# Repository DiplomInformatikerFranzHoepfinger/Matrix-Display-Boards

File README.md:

# Matrix-Display-Boards

## Inspiration

### Lytec

[CL3000 Photos](CL3000.md)

http://www.lytec.cn/CL3000?_l=en

http://www.lytec.cn/CL3000-N?product_id=37&_l=en

### Adafruit

https://github.com/adafruit/Adafruit-MatrixPortal-S3-PCB

### SmartMatrix / pixelmatix

https://community.pixelmatix.com/t/want-to-drive-a-hub08-display/1491

https://github.com/pixelmatix/SmartMatrix

https://github.com/pixelmatix/SmartMatrix/tree/master/extras/hardware

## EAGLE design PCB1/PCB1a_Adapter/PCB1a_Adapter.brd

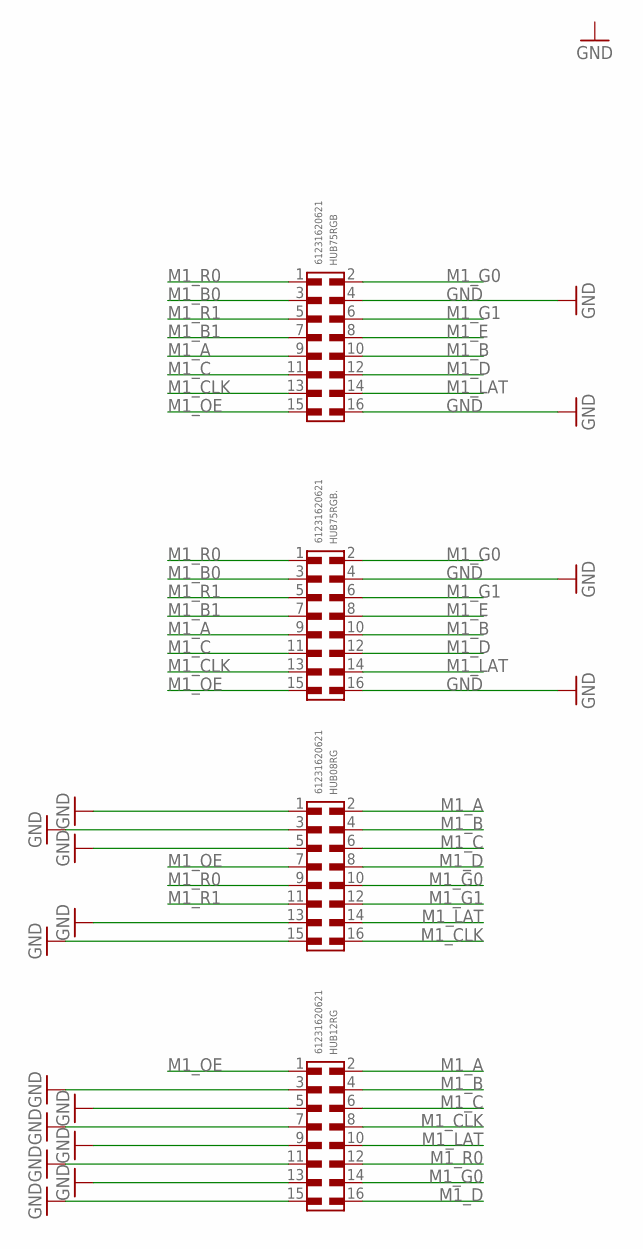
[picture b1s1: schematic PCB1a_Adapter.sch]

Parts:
HUB08RG, HUB12RG, HUB75RGB, HUB75RGB.: 61231620621

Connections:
GND: HUB08RG.1, HUB08RG.3, HUB08RG.5, HUB08RG.13, HUB08RG.15, HUB12RG.3, HUB12RG.5, HUB12RG.7, HUB12RG.9, HUB12RG.11, HUB12RG.13, HUB12RG.15, HUB75RGB.4, HUB75RGB.16, HUB75RGB..4, HUB75RGB..16
M1_A: HUB08RG.2, HUB12RG.2, HUB75RGB.9, HUB75RGB..9
M1_B: HUB08RG.4, HUB12RG.4, HUB75RGB.10, HUB75RGB..10
M1_B0: HUB75RGB.3, HUB75RGB..3
M1_B1: HUB75RGB.7, HUB75RGB..7
M1_C: HUB08RG.6, HUB12RG.6, HUB75RGB.11, HUB75RGB..11
M1_CLK: HUB08RG.16, HUB12RG.8, HUB75RGB.13, HUB75RGB..13
M1_D: HUB08RG.8, HUB12RG.16, HUB75RGB.12, HUB75RGB..12
M1_E: HUB75RGB.8, HUB75RGB..8
M1_G0: HUB08RG.10, HUB12RG.14, HUB75RGB.2, HUB75RGB..2
M1_G1: HUB08RG.12, HUB75RGB.6, HUB75RGB..6
M1_LAT: HUB08RG.14, HUB12RG.10, HUB75RGB.14, HUB75RGB..14
M1_OE: HUB08RG.7, HUB12RG.1, HUB75RGB.15, HUB75RGB..15
M1_R0: HUB08RG.9, HUB12RG.12, HUB75RGB.1, HUB75RGB..1
M1_R1: HUB08RG.11, HUB75RGB.5, HUB75RGB..5

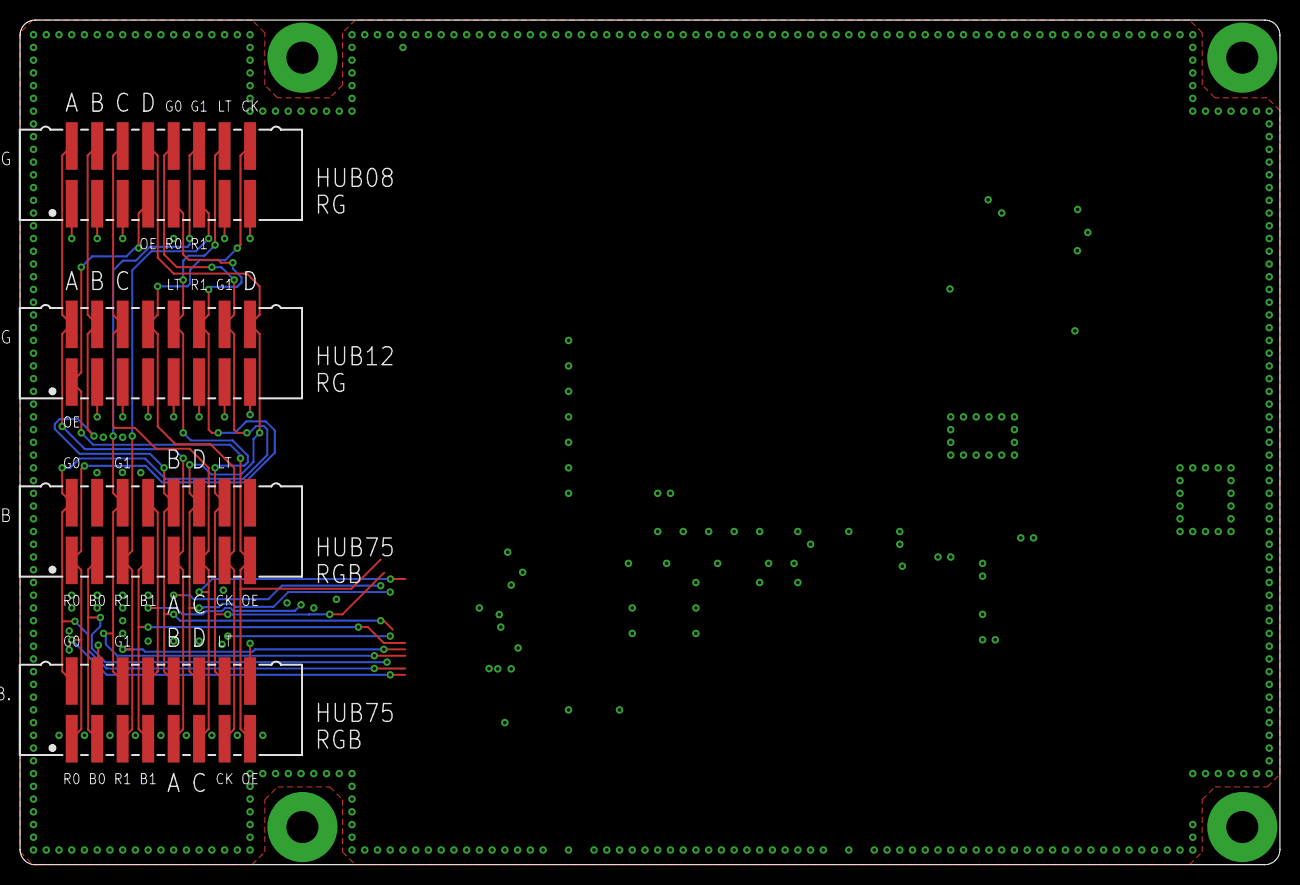
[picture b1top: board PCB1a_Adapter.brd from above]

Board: 2 copper layers, 125.6 x 84.2 mm, 4 parts (0 on the bottom side), 15 nets.

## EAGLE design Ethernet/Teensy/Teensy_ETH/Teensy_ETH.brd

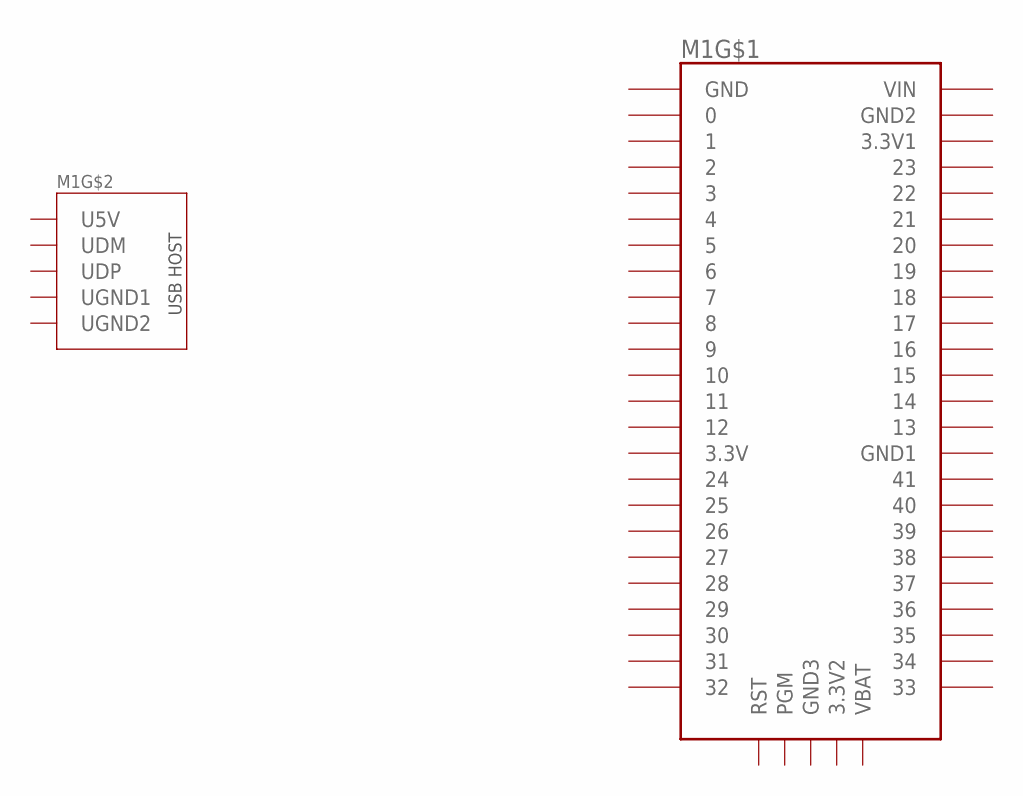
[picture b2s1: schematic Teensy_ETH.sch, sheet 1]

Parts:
M1: TEENSY4.1

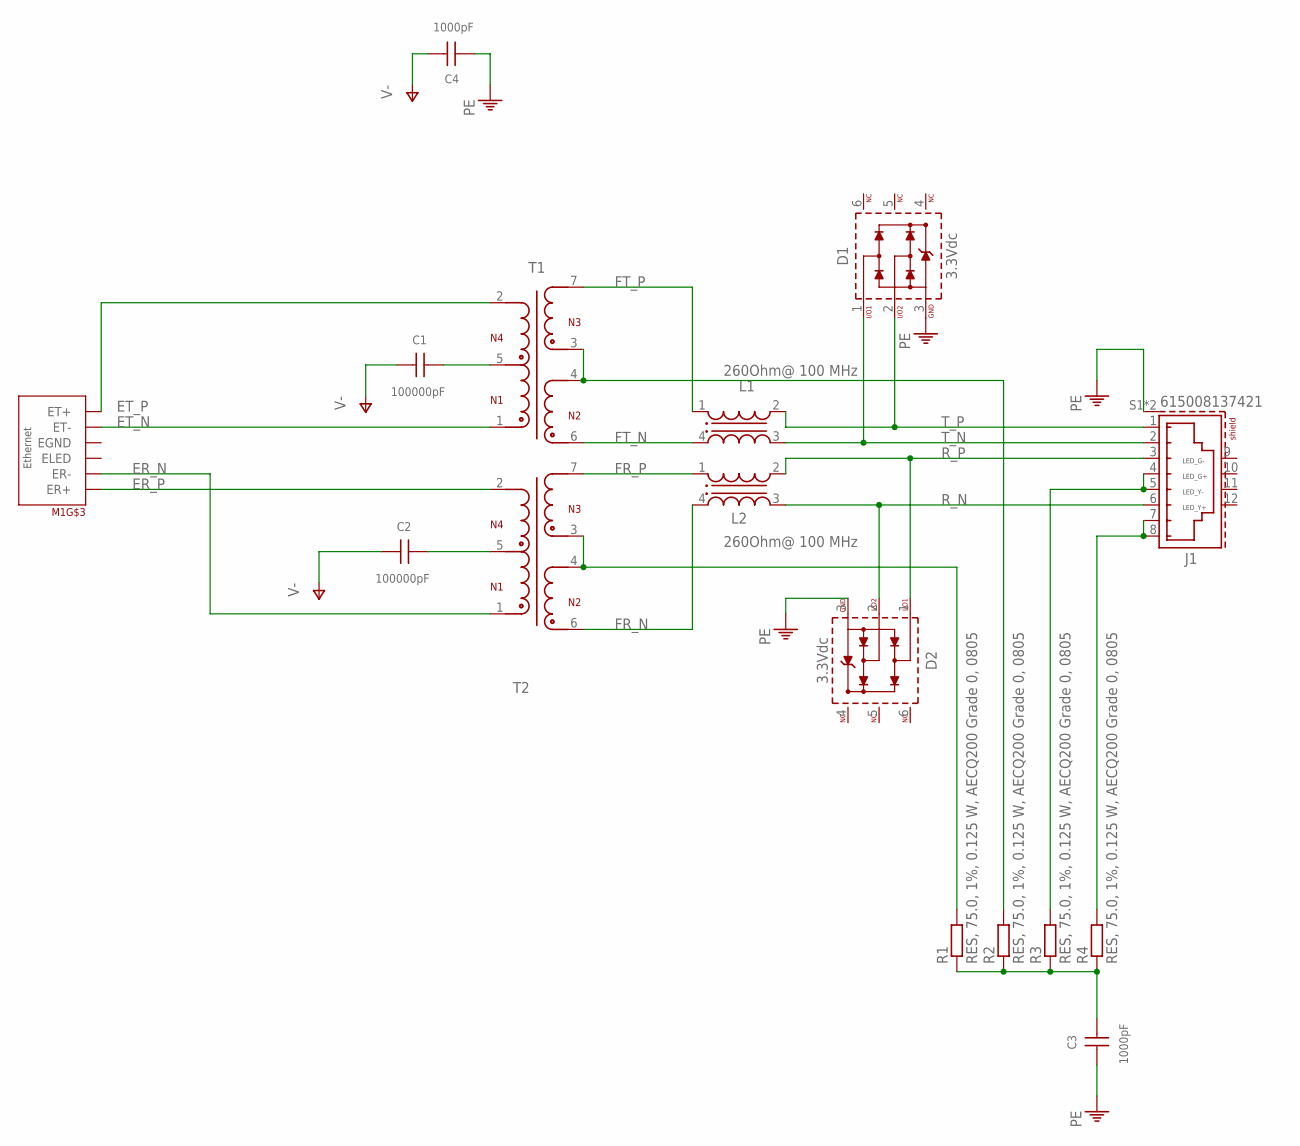
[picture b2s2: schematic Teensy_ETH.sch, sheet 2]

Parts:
C1, C2: 100000pF; WCAP-CSST_0603_R
C3, C4: 1000pF; WCAP-CSMH_1206_H1.6_R
D1, D2: 3.3Vdc; WE-TVS_DFN1210-6L
J1: 615008137421
L1, L2: 260Ohm@ 100 MHz; WE-CNSW_0805
M1: TEENSY4.1
R1, R2, R3, R4: RES, 75.0, 1%, 0.125 W, AECQ200 Grade 0, 0805; R0805
T1, T2: WE-STST_4532_74930000; WE-STST_74930000

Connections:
ER_N: M1.ER-, T2.1
ER_P: M1.ER+, T2.2
ET_N: M1.ET+ (ET-), T1.1
ET_P: M1.ET- (ET+), T1.2
FR_N: L2.4 (1), T2.6
FR_P: L2.1 (4), T2.7
FT_N: L1.4 (1), T1.6
FT_P: L1.1 (4), T1.7
unnamed: R2.2, T1.3, T1.4
unnamed: R1.2, T2.3, T2.4
unnamed: J1.4, J1.5, R3.2
unnamed: J1.7, J1.8, R4.2
unnamed: C1.2, T1.5
unnamed: C2.2, T2.5
unnamed: C3.2, R1.1, R2.1, R3.1, R4.1
PE: C3.1, C4.1, D1.3 (GND), D2.3 (GND), J1.S1 (SHIELD), J1.S2 (SHIELD)
R_N: D2.2 (I/O2), J1.6, L2.3 (2)
R_P: D2.1 (I/O1), J1.3, L2.2 (3)
T_N: D1.1 (I/O1), J1.2, L1.3 (2)
T_P: D1.2 (I/O2), J1.1, L1.2 (3)
V-: C1.1, C2.1, C4.2

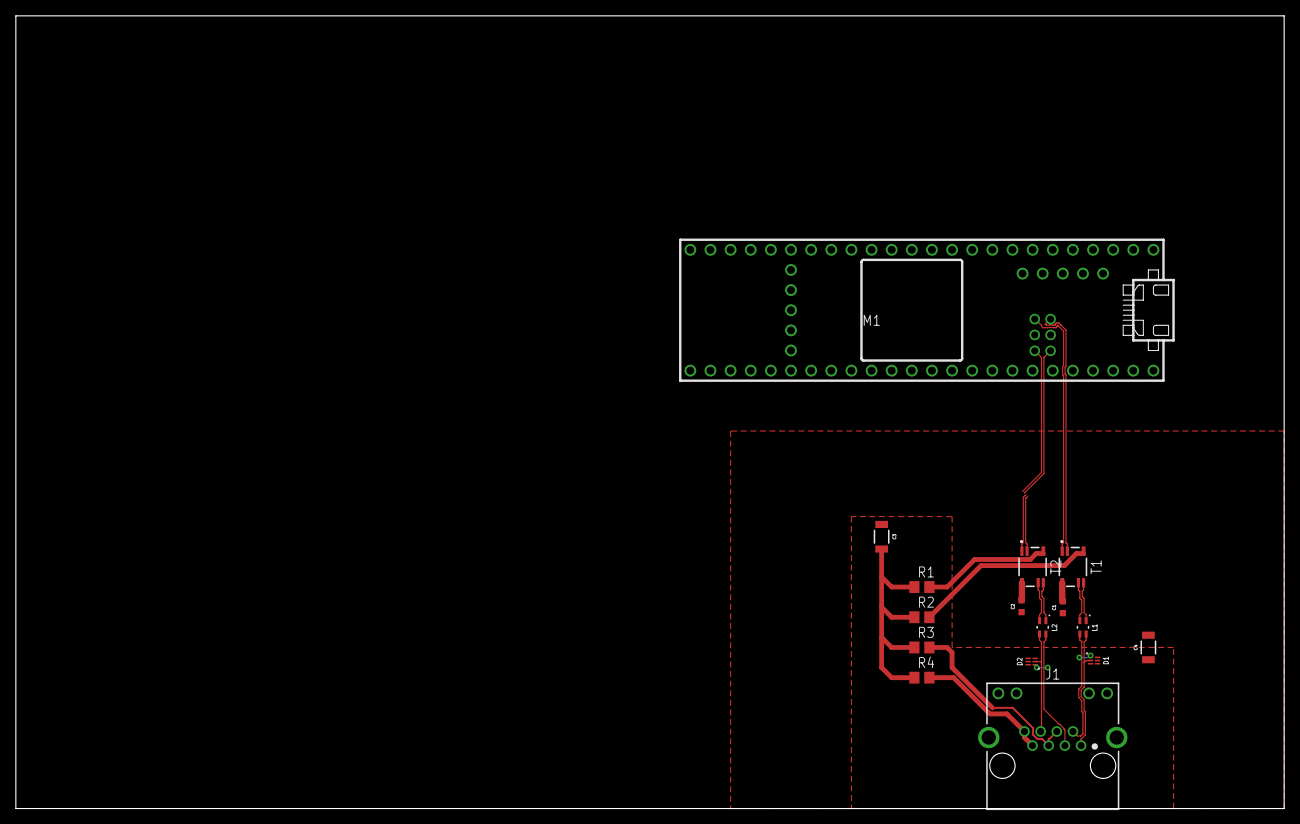
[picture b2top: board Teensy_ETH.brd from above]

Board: 2 copper layers, 160.0 x 100.0 mm, 16 parts (0 on the bottom side), 21 nets.

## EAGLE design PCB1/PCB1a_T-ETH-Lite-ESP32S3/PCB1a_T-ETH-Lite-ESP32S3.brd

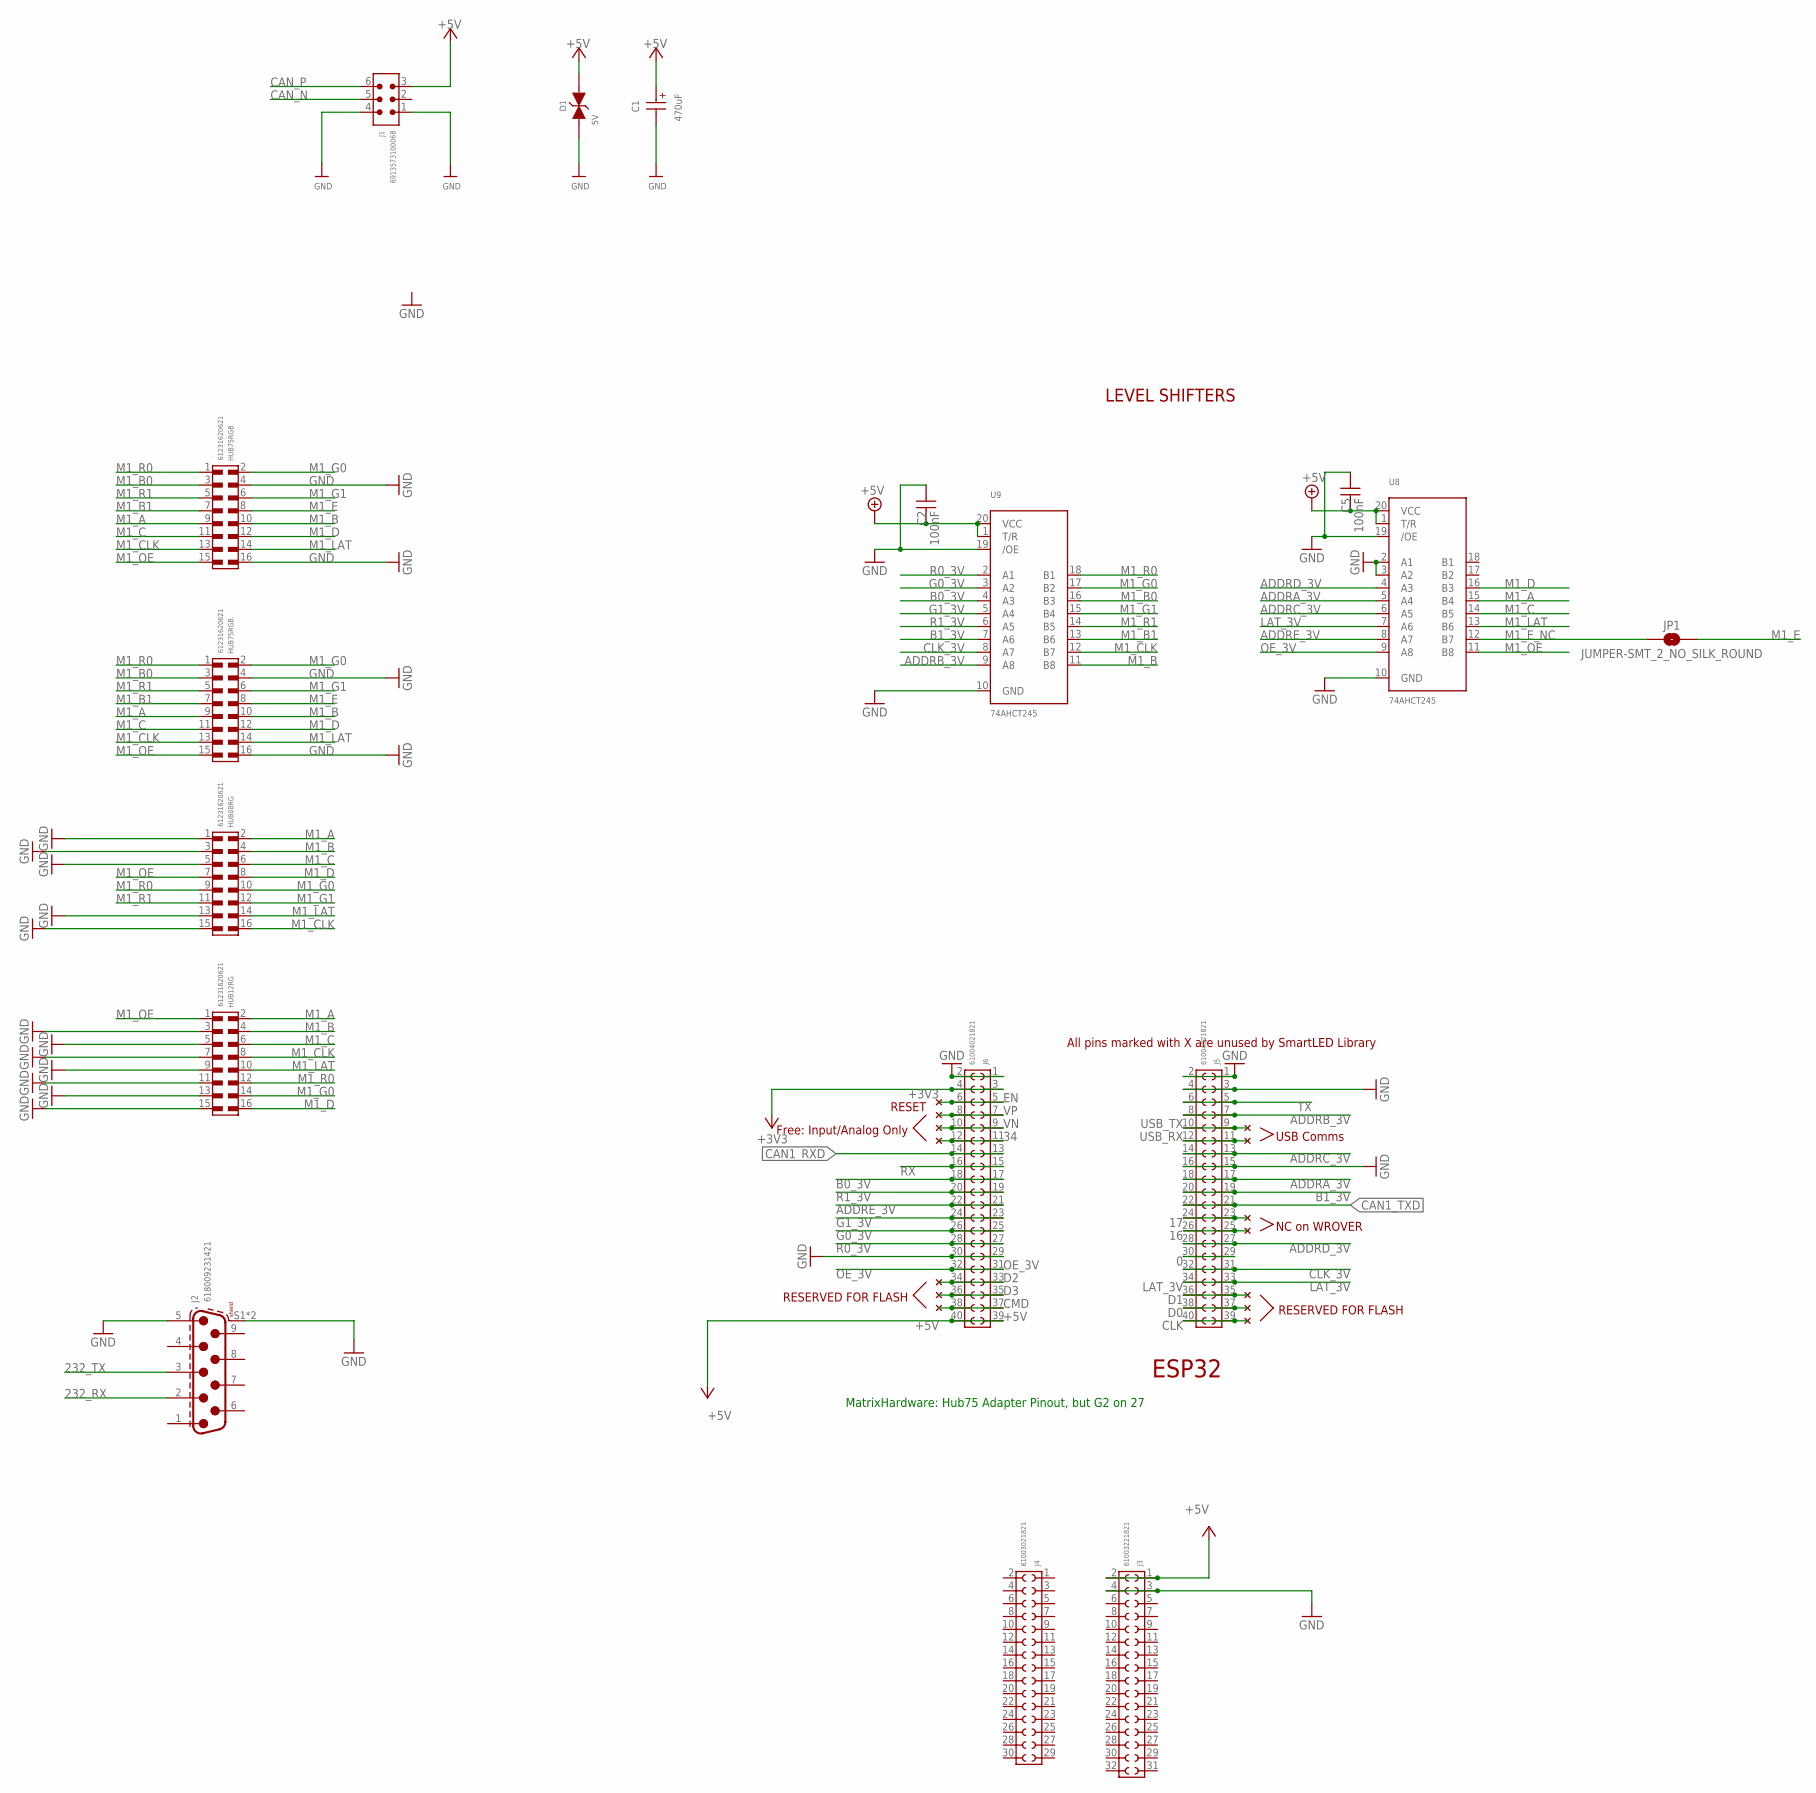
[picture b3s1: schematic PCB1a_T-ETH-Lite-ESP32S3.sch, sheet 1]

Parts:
C1: 470uF; WCAP-AS5H_10X10.5(DXL)
C2, C5: 100nF; WCAP-CSGP_0805_H0.8_R
D1: 5V; WE-TVSP_DO-214AB_BIDIRECTIONAL
HUB08RG, HUB12RG, HUB75RGB, HUB75RGB.: 61231620621
J1: 691357310006B
J2: 618009231421
J3: 61003221821
J4: 61003021821
J5, J6: 61004021821
JP1: JUMPER-SMT_2_NO_SILK_ROUND; SMT-JUMPER_2_NO_SILK_ROUND
U8, U9: 74AHCT245; TSSOP20

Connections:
0: J5.29, J5.30
16: J5.25, J5.26
17: J5.23, J5.24
34: J6.11, J6.12
232_RX: J2.2; also elsewhere on the board
232_TX: J2.3; also elsewhere on the board
+3V3: J6.3, J6.4; also elsewhere on the board
+5V: C1.1 (+), C2.2, C5.2, D1.2, J1.3, J3.1, J3.2, J6.39, J6.40, U8.1 (T/R), U8.20 (VCC), U9.1 (T/R), U9.20 (VCC); also elsewhere on the board
ADDRA_3V: J5.17, J5.18, U8.5 (A4)
ADDRB_3V: J5.7, J5.8, U9.9 (A8)
ADDRC_3V: J5.13, J5.14, U8.6 (A5)
ADDRD_3V: J5.27, J5.28, U8.4 (A3)
ADDRE_3V: J6.21, J6.22, U8.8 (A7)
B0_3V: J6.17, J6.18, U9.4 (A3)
B1_3V: J5.19, J5.20, U9.7 (A6)
CAN1_RXD: J6.13, J6.14; also elsewhere on the board
CAN1_TXD: J5.21, J5.22; also elsewhere on the board
CAN_N: J1.5; also elsewhere on the board
CAN_P: J1.6; also elsewhere on the board
CLK: J5.39, J5.40
CLK_3V: J5.31, J5.32, U9.8 (A7)
CMD: J6.37, J6.38
D0: J5.37, J5.38
D1: J5.35, J5.36
D2: J6.33, J6.34
D3: J6.35, J6.36
EN: J6.5, J6.6
G0_3V: J6.25, J6.26, U9.3 (A2)
G1_3V: J6.23, J6.24, U9.5 (A4)
GND: C1.2 (-), C2.1, C5.1, D1.1, HUB08RG.1, HUB08RG.3, HUB08RG.5, HUB08RG.13, HUB08RG.15, HUB12RG.3, HUB12RG.5, HUB12RG.7, HUB12RG.9, HUB12RG.11, HUB12RG.13, HUB12RG.15, HUB75RGB.4, HUB75RGB.16, HUB75RGB..4, HUB75RGB..16, J1.1, J1.4, J2.5, J2.S1 (SHIELD), J2.S2 (SHIELD), J3.3, J3.4, J5.1, J5.2, J5.3, J5.4, J5.15, J5.16, J6.1, J6.2, J6.29, J6.30, U8.2 (A1), U8.3 (A2), U8.10 (GND), U8.19 (/OE), U9.10 (GND), U9.19 (/OE); also elsewhere on the board
LAT_3V: J5.33, J5.34, U8.7 (A6)
M1_A: HUB08RG.2, HUB12RG.2, HUB75RGB.9, HUB75RGB..9, U8.15 (B4)
M1_B: HUB08RG.4, HUB12RG.4, HUB75RGB.10, HUB75RGB..10, U9.11 (B8)
M1_B0: HUB75RGB.3, HUB75RGB..3, U9.16 (B3)
M1_B1: HUB75RGB.7, HUB75RGB..7, U9.13 (B6)
M1_C: HUB08RG.6, HUB12RG.6, HUB75RGB.11, HUB75RGB..11, U8.14 (B5)
M1_CLK: HUB08RG.16, HUB12RG.8, HUB75RGB.13, HUB75RGB..13, U9.12 (B7)
M1_D: HUB08RG.8, HUB12RG.16, HUB75RGB.12, HUB75RGB..12, U8.16 (B3)
M1_E: HUB75RGB.8, HUB75RGB..8, JP1.2
M1_E_NC: JP1.1, U8.12 (B7)
M1_G0: HUB08RG.10, HUB12RG.14, HUB75RGB.2, HUB75RGB..2, U9.17 (B2)
M1_G1: HUB08RG.12, HUB75RGB.6, HUB75RGB..6, U9.15 (B4)
M1_LAT: HUB08RG.14, HUB12RG.10, HUB75RGB.14, HUB75RGB..14, U8.13 (B6)
M1_OE: HUB08RG.7, HUB12RG.1, HUB75RGB.15, HUB75RGB..15, U8.11 (B8)
M1_R0: HUB08RG.9, HUB12RG.12, HUB75RGB.1, HUB75RGB..1, U9.18 (B1)
M1_R1: HUB08RG.11, HUB75RGB.5, HUB75RGB..5, U9.14 (B5)
OE_3V: J6.31, J6.32, U8.9 (A8)
R0_3V: J6.27, J6.28, U9.2 (A1)
R1_3V: J6.19, J6.20, U9.6 (A5)
RX: J6.15, J6.16; also elsewhere on the board
TX: J5.5, J5.6; also elsewhere on the board
USB_RX: J5.11, J5.12
USB_TX: J5.9, J5.10
VN: J6.9, J6.10
VP: J6.7, J6.8

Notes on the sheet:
LEVEL SHIFTERS
ESP32
All pins marked with X are unused by SmartLED Library
RESERVED FOR FLASH
Free: Input/Analog Only
RESET
USB Comms
NC on WROVER
MatrixHardware: Hub75 Adapter Pinout, but G2 on 27

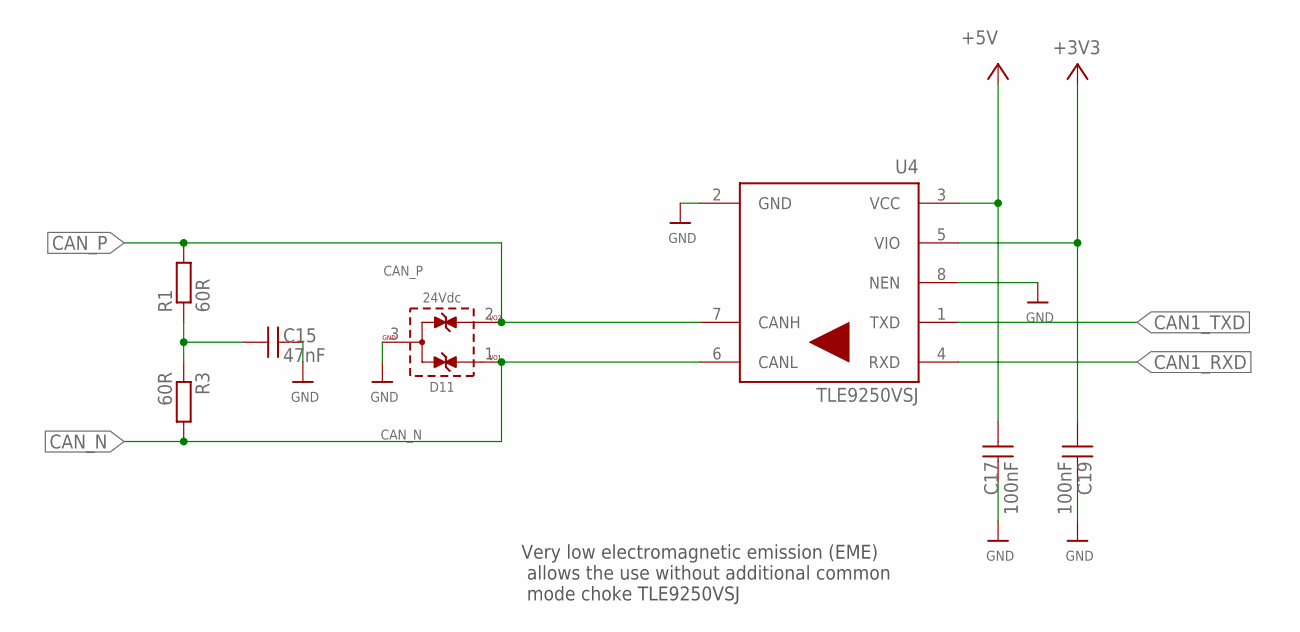
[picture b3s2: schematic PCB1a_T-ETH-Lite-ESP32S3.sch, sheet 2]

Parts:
C15: 47nF; WCAP-CSGP_0805_H0.8_R
C17, C19: 100nF; WCAP-CSGP_0805_H0.8_R
D11: 24Vdc; WE-TVS_SOT23-3L
R1, R3: 60R; R0805
U4: TLE9250VSJ; SOIC127P602X173-8N-V

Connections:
+3V3: C19.1, U4.5 (VIO); also elsewhere on the board
+5V: C17.1, U4.3 (VCC); also elsewhere on the board
CAN1_RXD: U4.4 (RXD); also elsewhere on the board
CAN1_TXD: U4.1 (TXD); also elsewhere on the board
CAN_N: D11.1 (I/O1), R3.2, U4.6 (CANL); also elsewhere on the board
CAN_P: D11.2 (I/O2), R1.2, U4.7 (CANH); also elsewhere on the board
GND: C15.2, C17.2, C19.2, D11.3 (GND), U4.2 (GND), U4.8 (NEN); also elsewhere on the board
unnamed: C15.1, R1.1, R3.1

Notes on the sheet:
Very low electromagnetic emission (EME) allows the use without additional common mode choke TLE9250VSJ

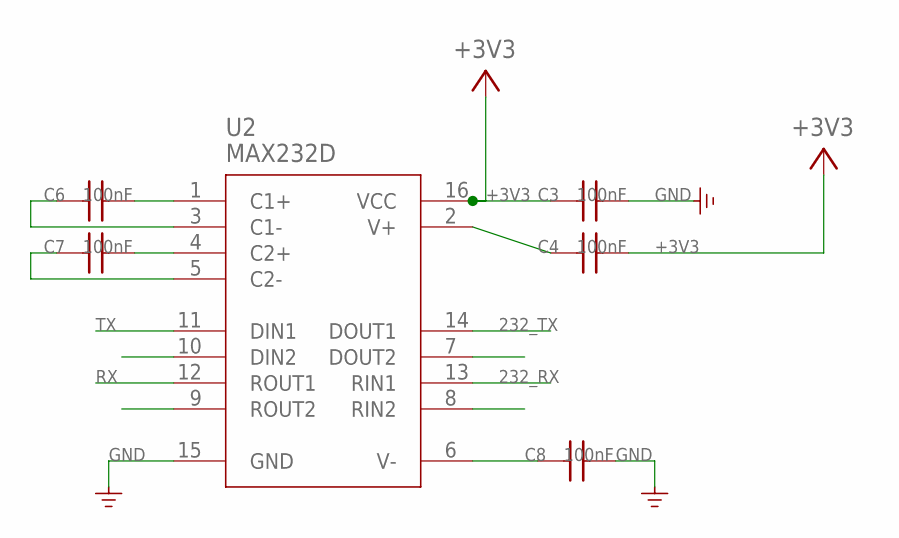
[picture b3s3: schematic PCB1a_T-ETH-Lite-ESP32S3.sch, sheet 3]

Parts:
C3, C4, C6, C7, C8: 100nF; WCAP-CSGP_0805_H0.8_R
U2: MAX232D; SOIC16

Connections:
232_RX: U2.13 (RIN1); also elsewhere on the board
232_TX: U2.14 (DOUT1); also elsewhere on the board
+3V3: C3.1, C4.2, U2.16 (VCC); also elsewhere on the board
GND: C3.2, C8.2, U2.15 (GND); also elsewhere on the board
unnamed: C6.2, U2.1 (C1+)
unnamed: C6.1, U2.3 (C1-)
unnamed: C7.2, U2.4 (C2+)
unnamed: C7.1, U2.5 (C2-)
unnamed: C4.1, U2.2 (V+)
unnamed: C8.1, U2.6 (V-)
RX: U2.12 (ROUT1); also elsewhere on the board
TX: U2.11 (DIN1); also elsewhere on the board

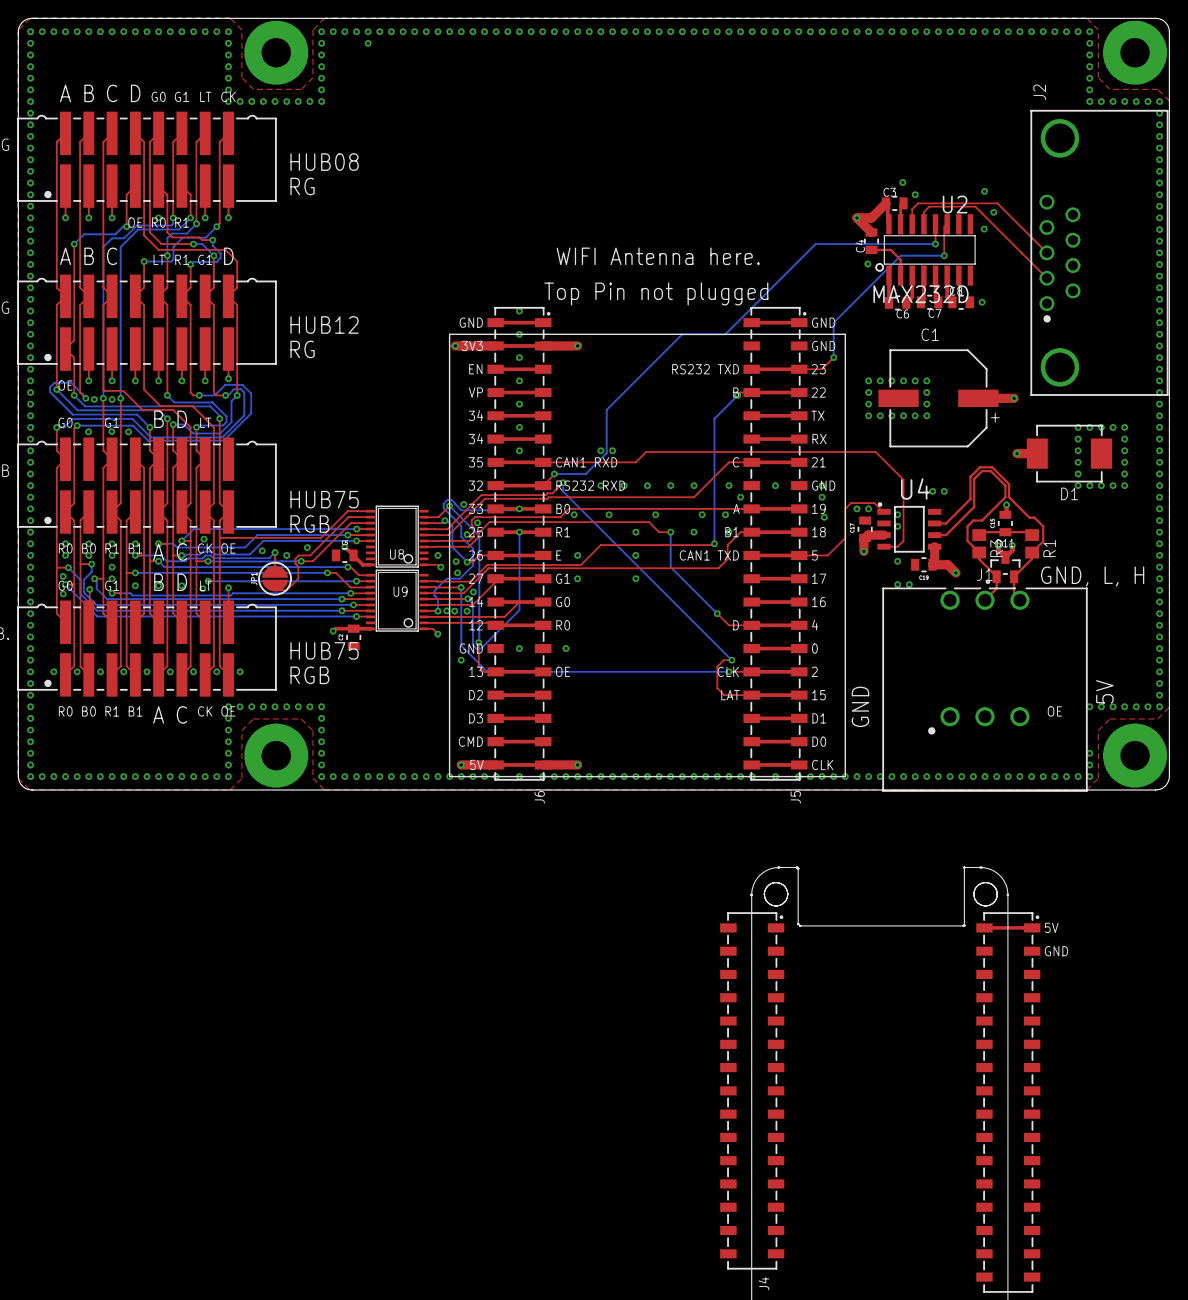
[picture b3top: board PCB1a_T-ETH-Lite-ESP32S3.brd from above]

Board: 4 copper layers, 125.6 x 84.2 mm, 30 parts (0 on the bottom side), 62 nets.

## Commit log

2024-01-12 Add .gitignore file to ignore temporary files
    This commit adds a new .gitignore file that includes patterns to ignore temporary files with extensions .b#, .s#, and .l#.
2024-01-12 Add Eagle configuration file
    This commit adds a new file, `eagle.epf`, which contains the configuration settings for Eagle version "09 06 02".
2024-01-12 Board Outline
2024-01-12 Mountholes and Outline Symmetric.
2024-01-12 Hole Dimensions Distance added.
2024-01-13 Platinen Grundmaße
2024-01-13 Rounded Rect.
2024-01-13 Outline done .
2024-01-13 Change visibility of "Measures" layer to visible in PCB1a.brd
    The commit message should be:
    "Update visibility of 'Measures' layer in PCB1a.brd"
2024-01-14 power Conn. added.
2024-01-14 ethernet remove for now.
2024-01-14 so far ...
2024-01-14 ESP32 added.
2024-01-14 intermediate. commit.
2024-01-15 thermals="no"/>
    thermals="no"/>
2024-01-16 thermals="no"
    thermals="no"
2024-01-17 copy over the Board and sch.
    for PCB1a_ESP32-DevKitC
2024-01-17 SMD Connectors.
2024-01-17 rm THT
2024-01-17 width="0.2032" -- 8 mil
2024-01-17 thermals="no"/>
    thermals="no"/>
2024-01-17 Go Production
2024-01-17 so, ORDER !
2024-01-17 copy over only.
2024-02-11 https://github.com/phil-barrett/grblHAL-teensy-4.x
2024-02-11 1st Version with WE WE-STST 74930000
    WE-STST 74930000
2024-02-11 sicherung
2024-02-15 Update Teensy_ETH project settings for Schematic and Board Editors
    - Updated the view coordinates for the Schematic Editor
    - Added a new window for the Board Editor
    - Updated the view coordinates for the Board Editor
    - Added a new window for the Control Panel
2024-10-04 Add Eagle version and platform info, set AutoSaveProject to 1, and include a long list of UsedLibraryUrns.
2024-10-04 Update PCB design settings and connector library description.
    - Update PCB design settings for vector font to "alwaysvectorfont=yes" and vertical text to "up".
    - Remove specific library references from the PCB design file.
    - Modify a connector library description in the board file.
2024-10-04 Update schematic and board editor settings, add new CSV and Excel files.
    - Updated editor types and file views
    - Changed wire bend settings
    - Added a new CSV file with component details
    - Included new Excel files for Bill of Materials

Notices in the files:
parts and their libraries:
Wurth_Signal: Copyright: Würth Elektronik
microbuilder: This work is placed in the public domain, and may be freely used for commercial and non-commercial work with the following conditions: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
